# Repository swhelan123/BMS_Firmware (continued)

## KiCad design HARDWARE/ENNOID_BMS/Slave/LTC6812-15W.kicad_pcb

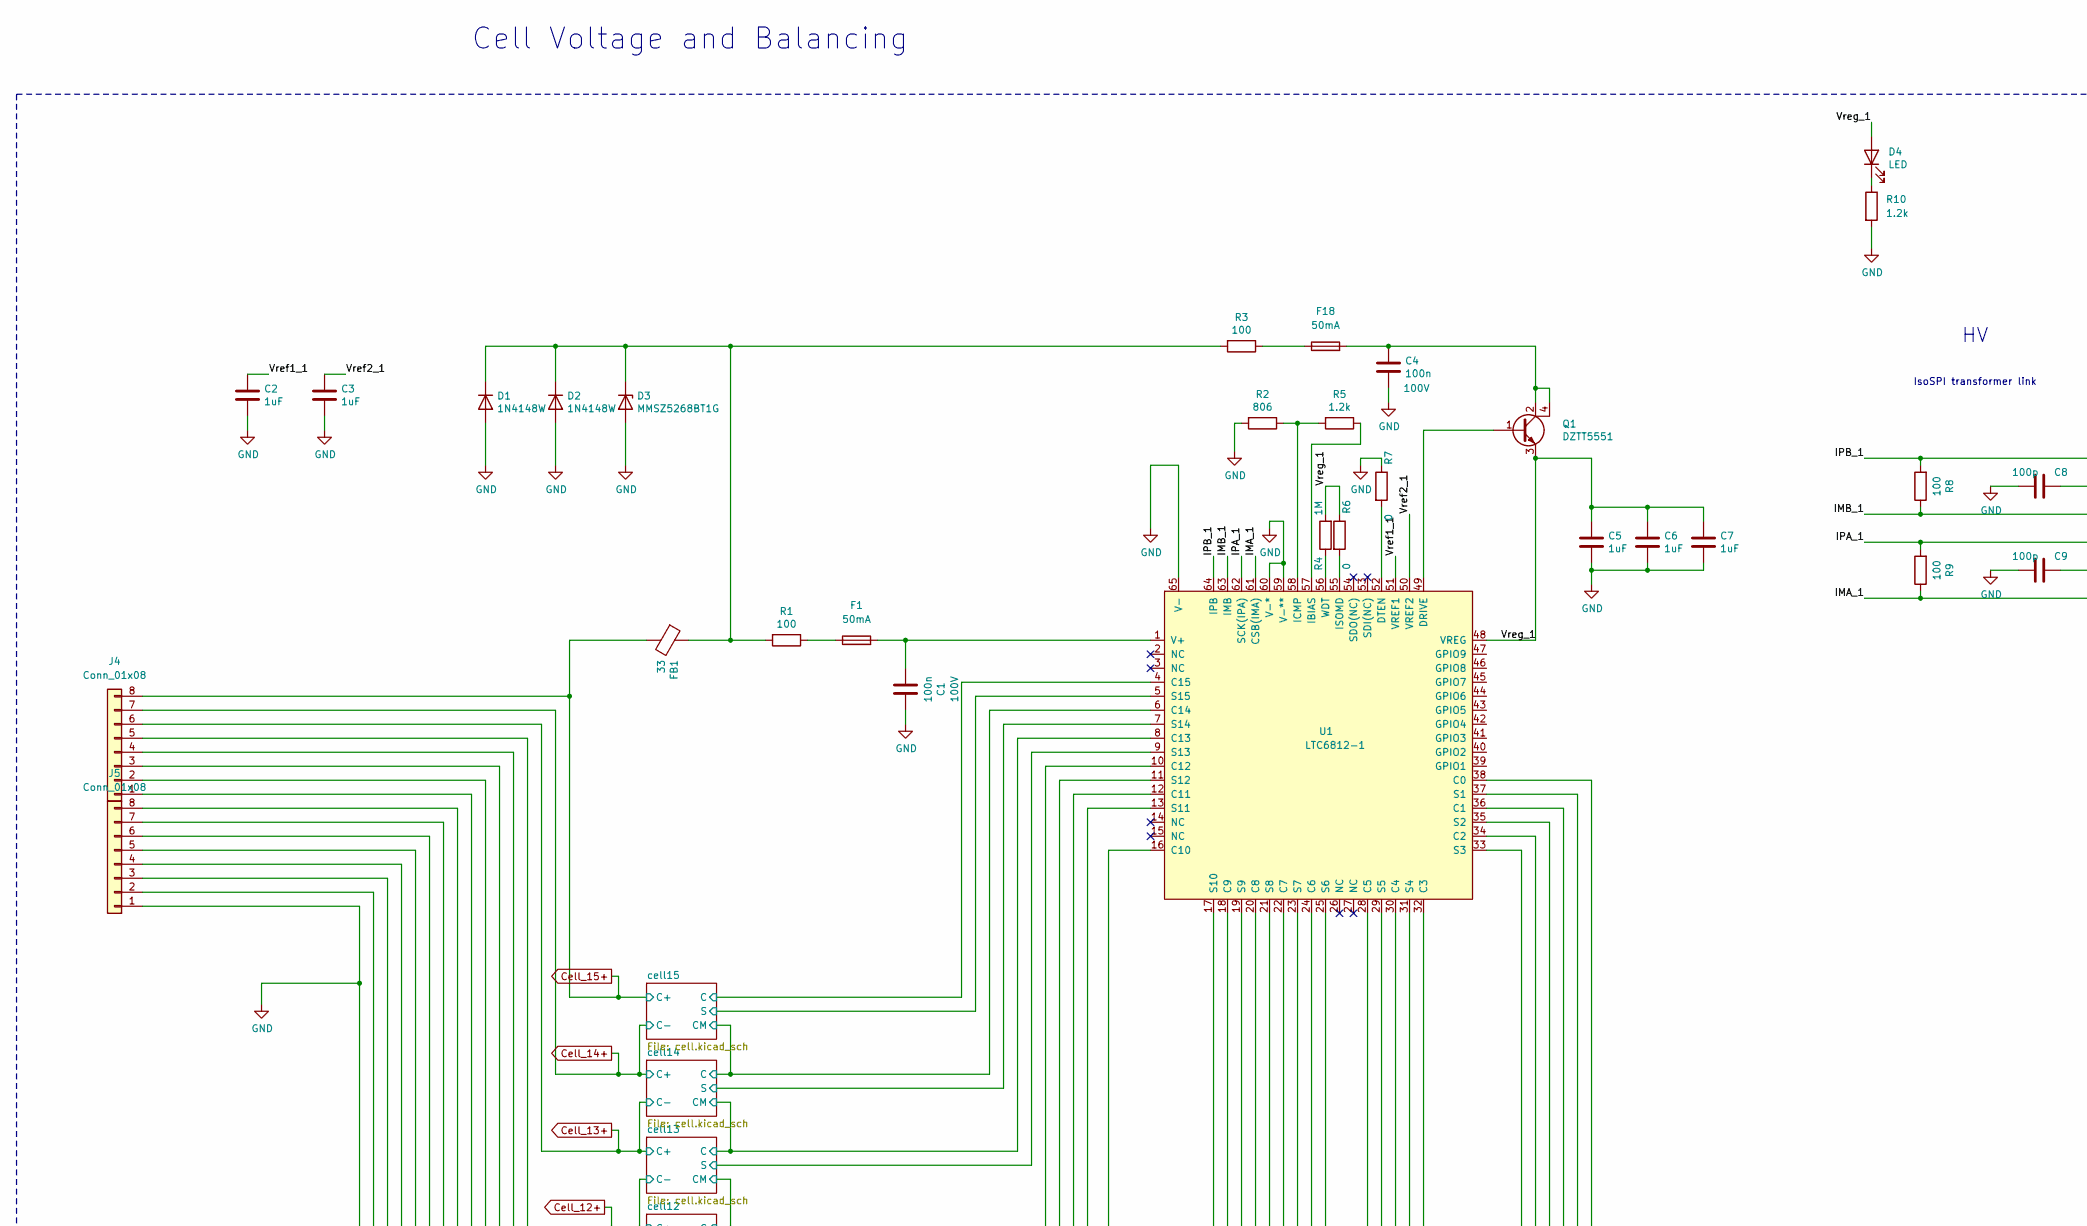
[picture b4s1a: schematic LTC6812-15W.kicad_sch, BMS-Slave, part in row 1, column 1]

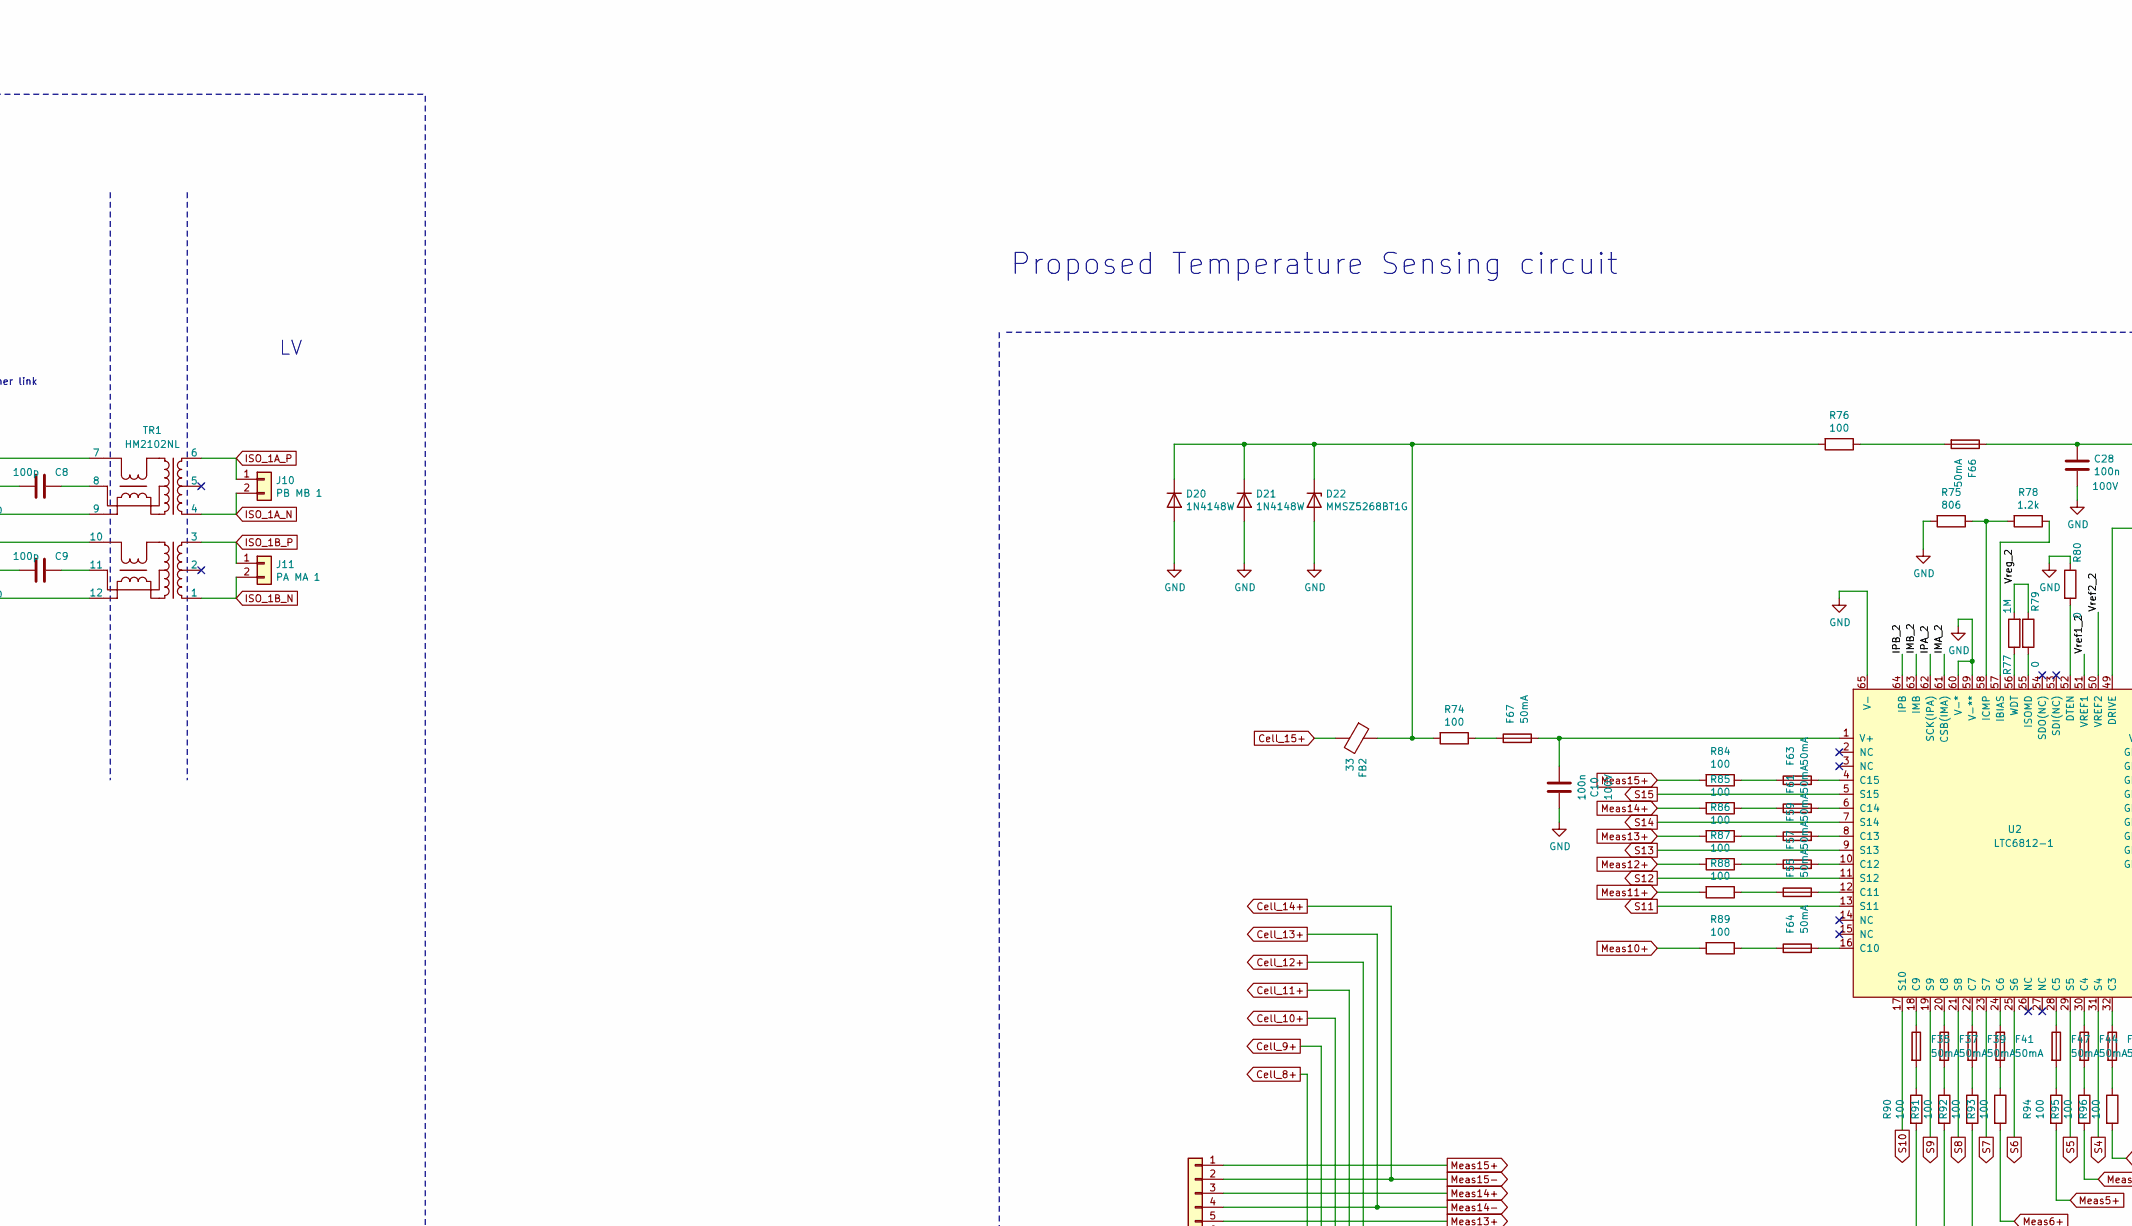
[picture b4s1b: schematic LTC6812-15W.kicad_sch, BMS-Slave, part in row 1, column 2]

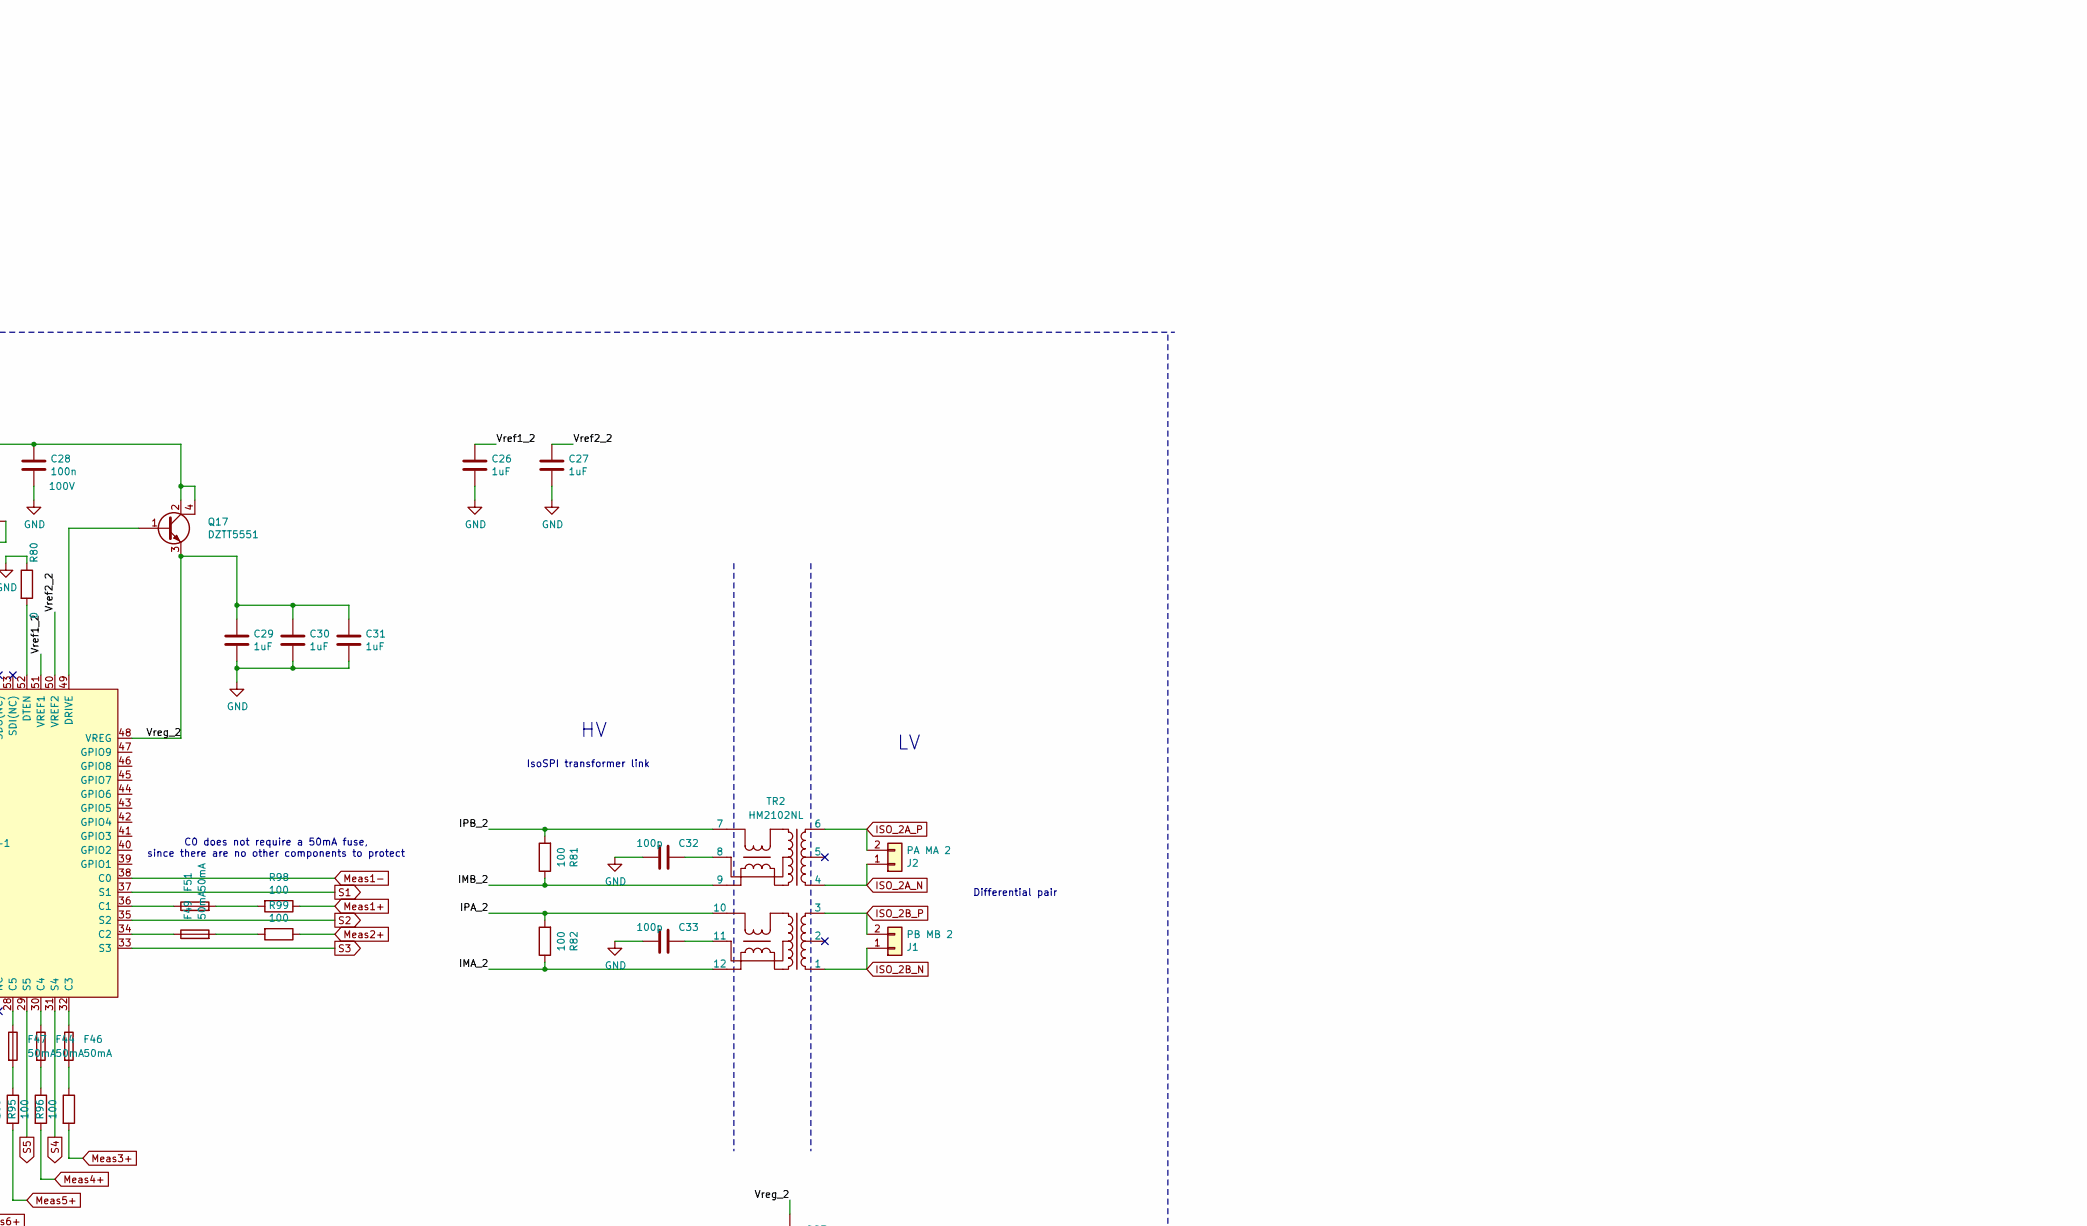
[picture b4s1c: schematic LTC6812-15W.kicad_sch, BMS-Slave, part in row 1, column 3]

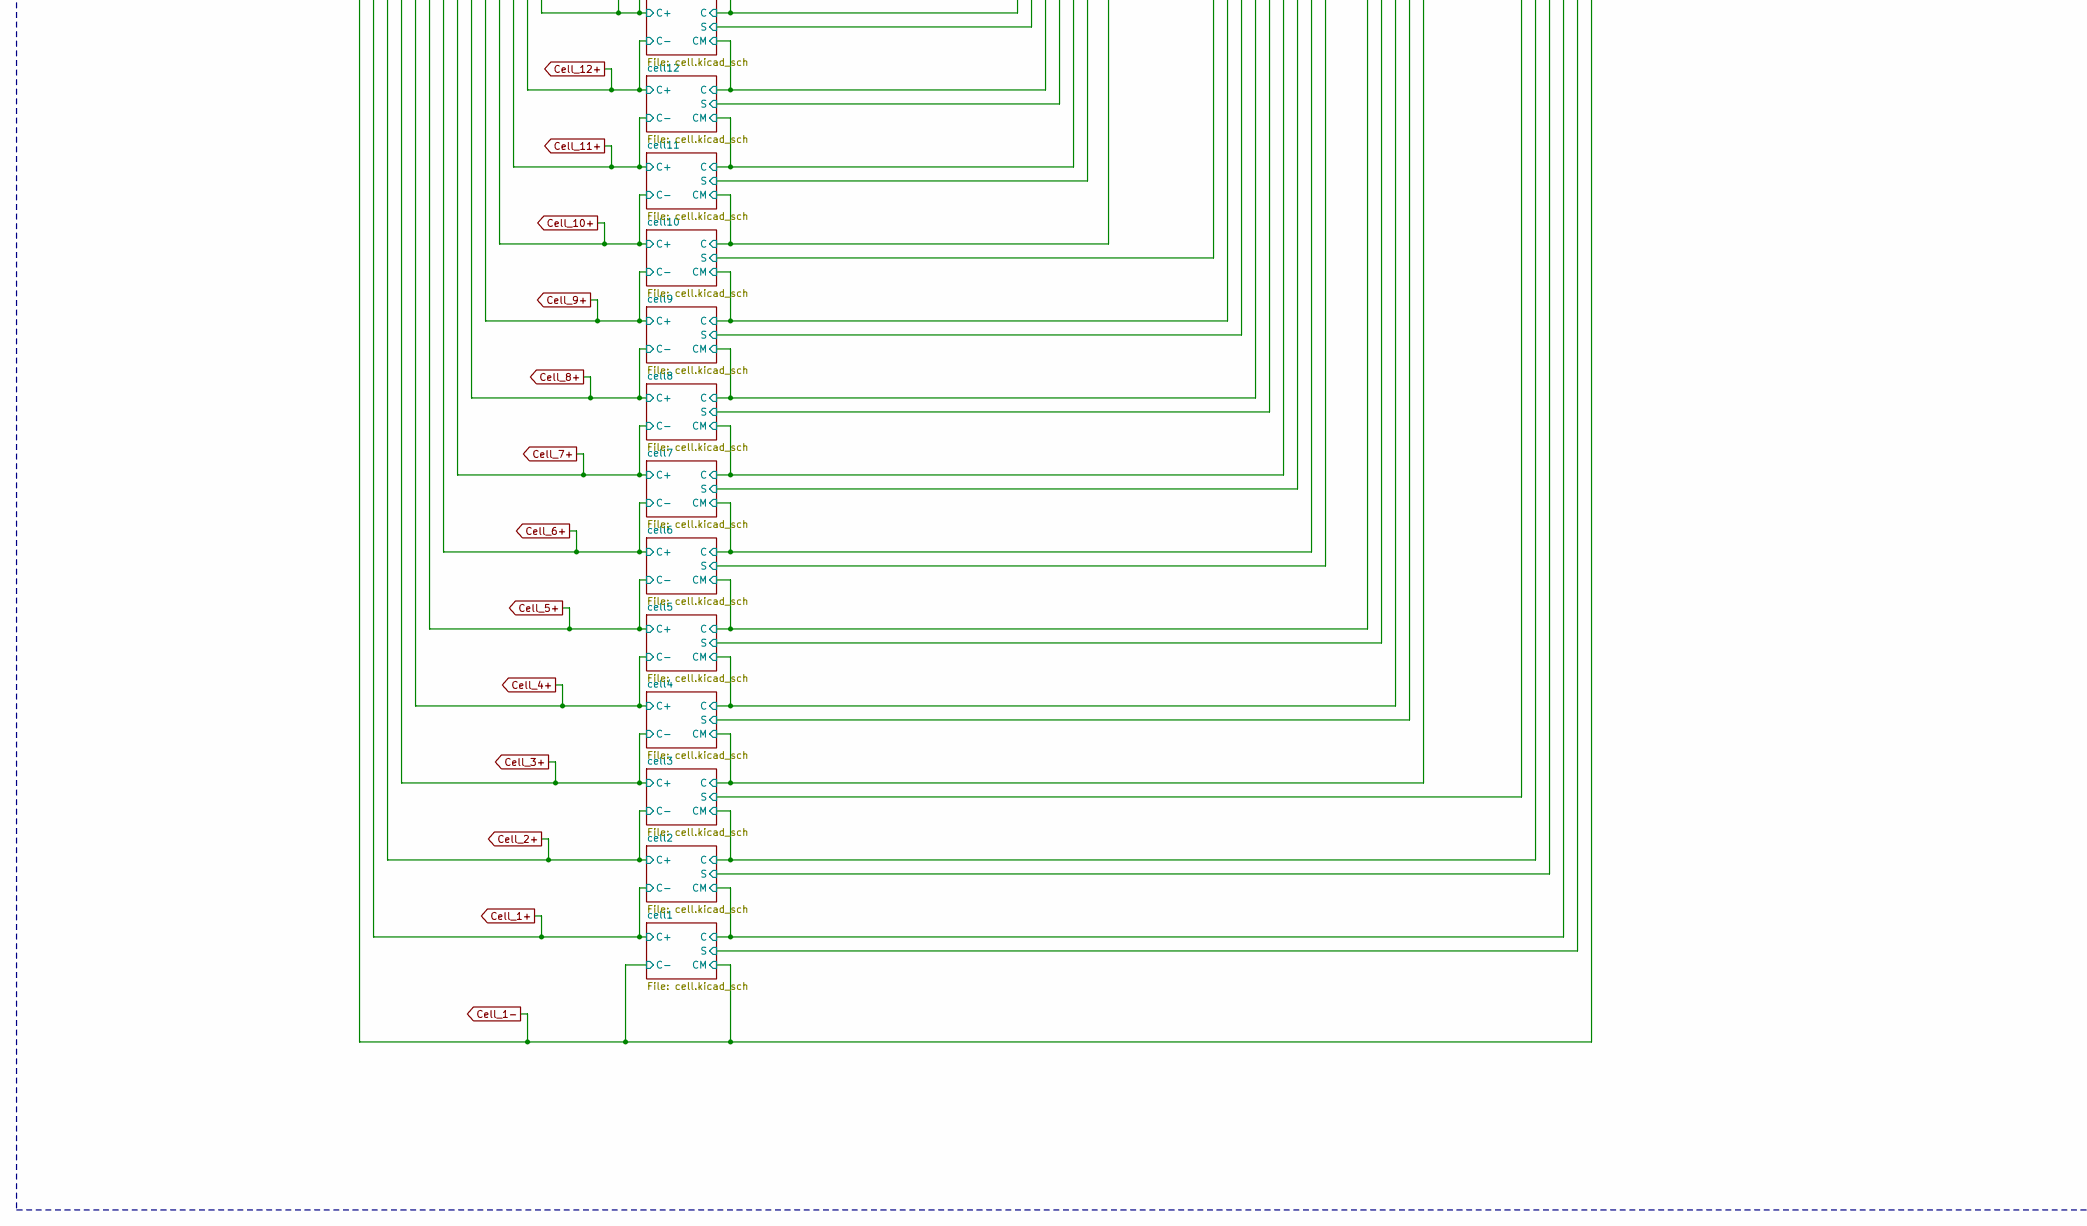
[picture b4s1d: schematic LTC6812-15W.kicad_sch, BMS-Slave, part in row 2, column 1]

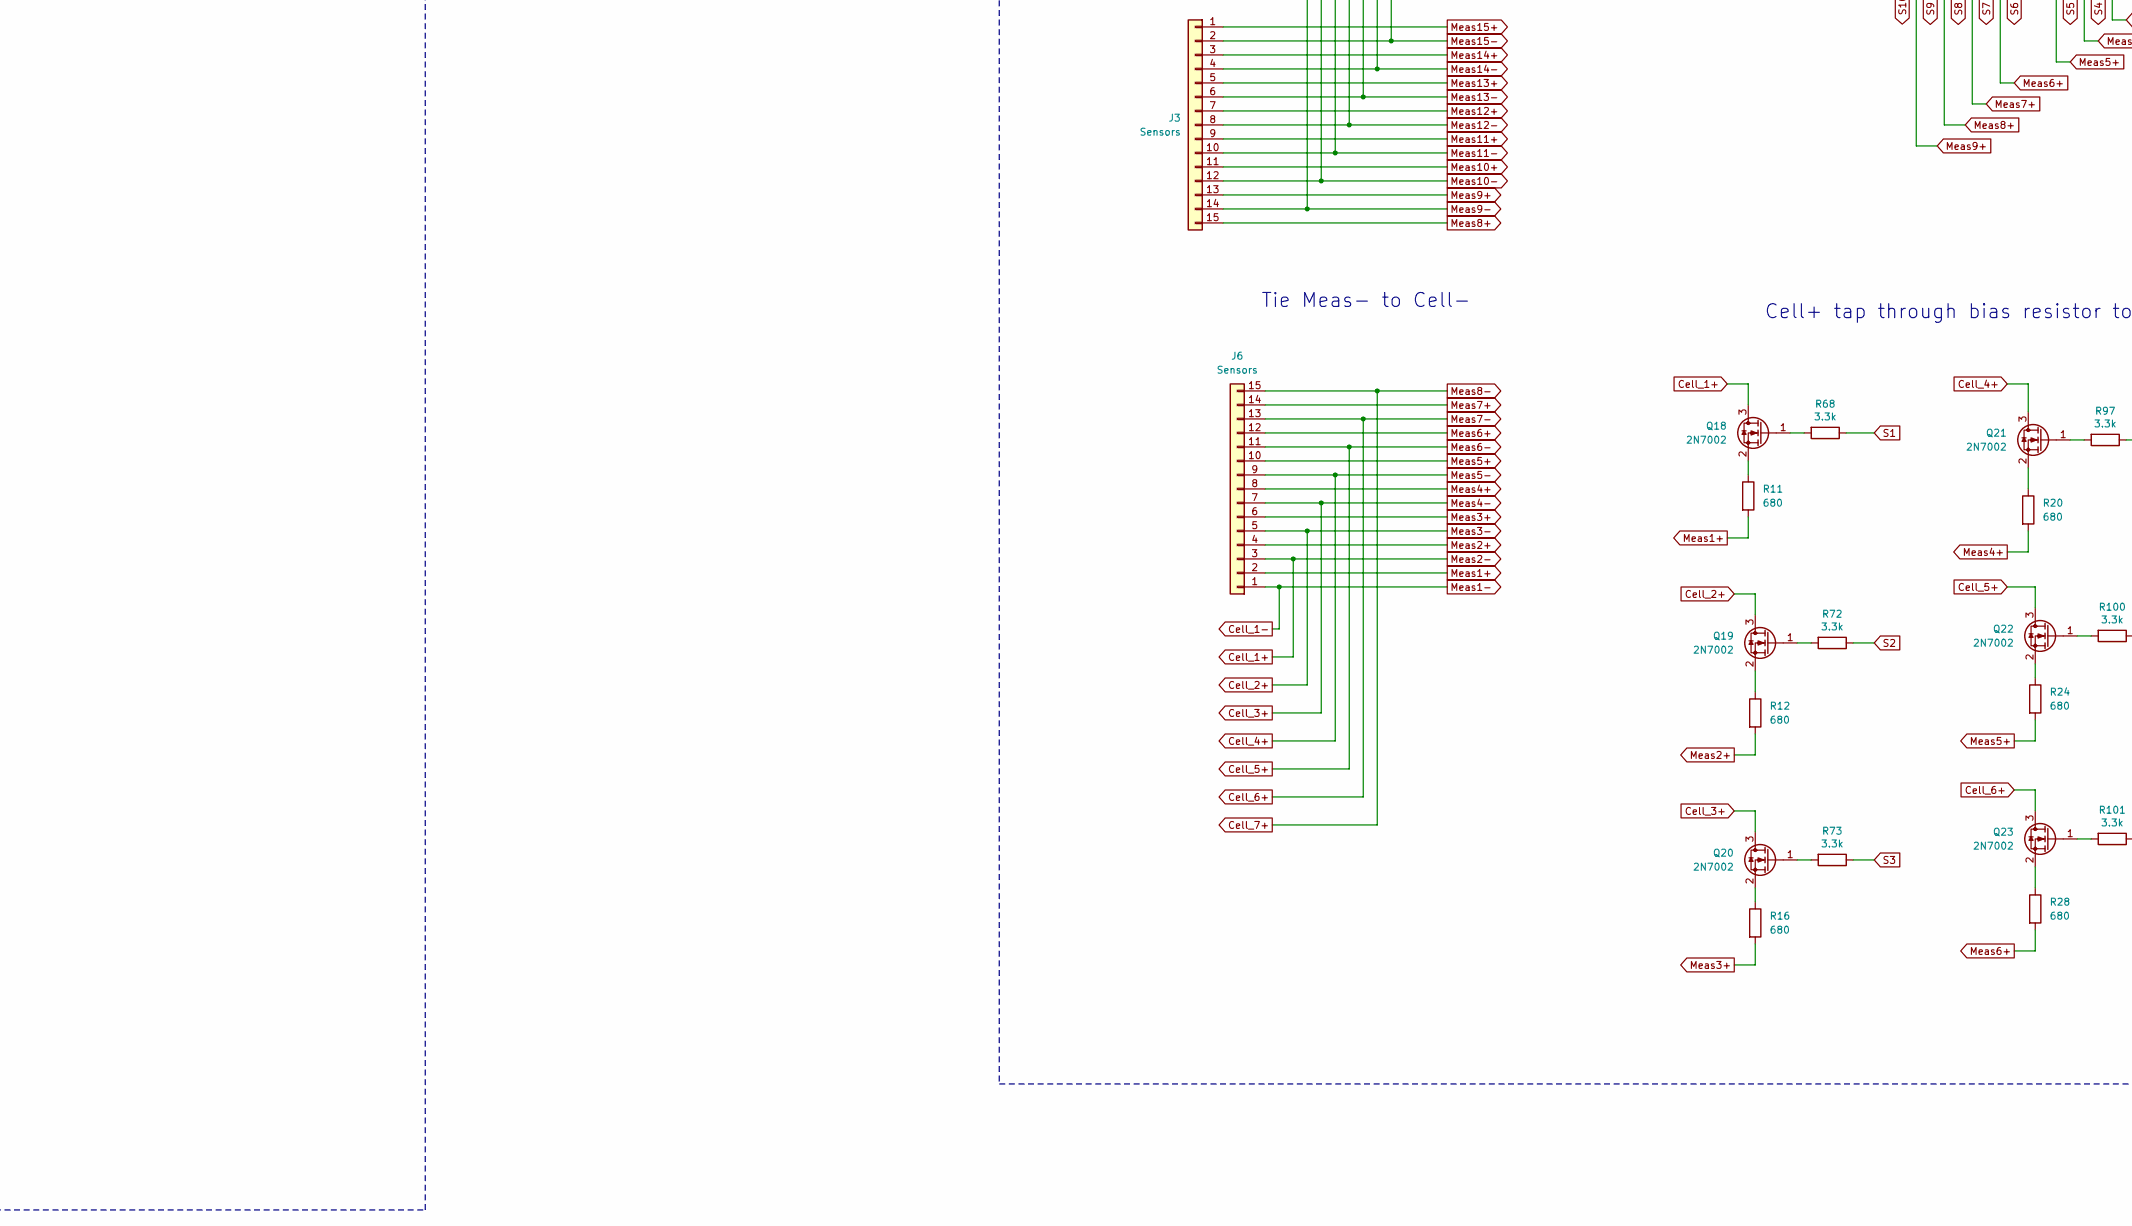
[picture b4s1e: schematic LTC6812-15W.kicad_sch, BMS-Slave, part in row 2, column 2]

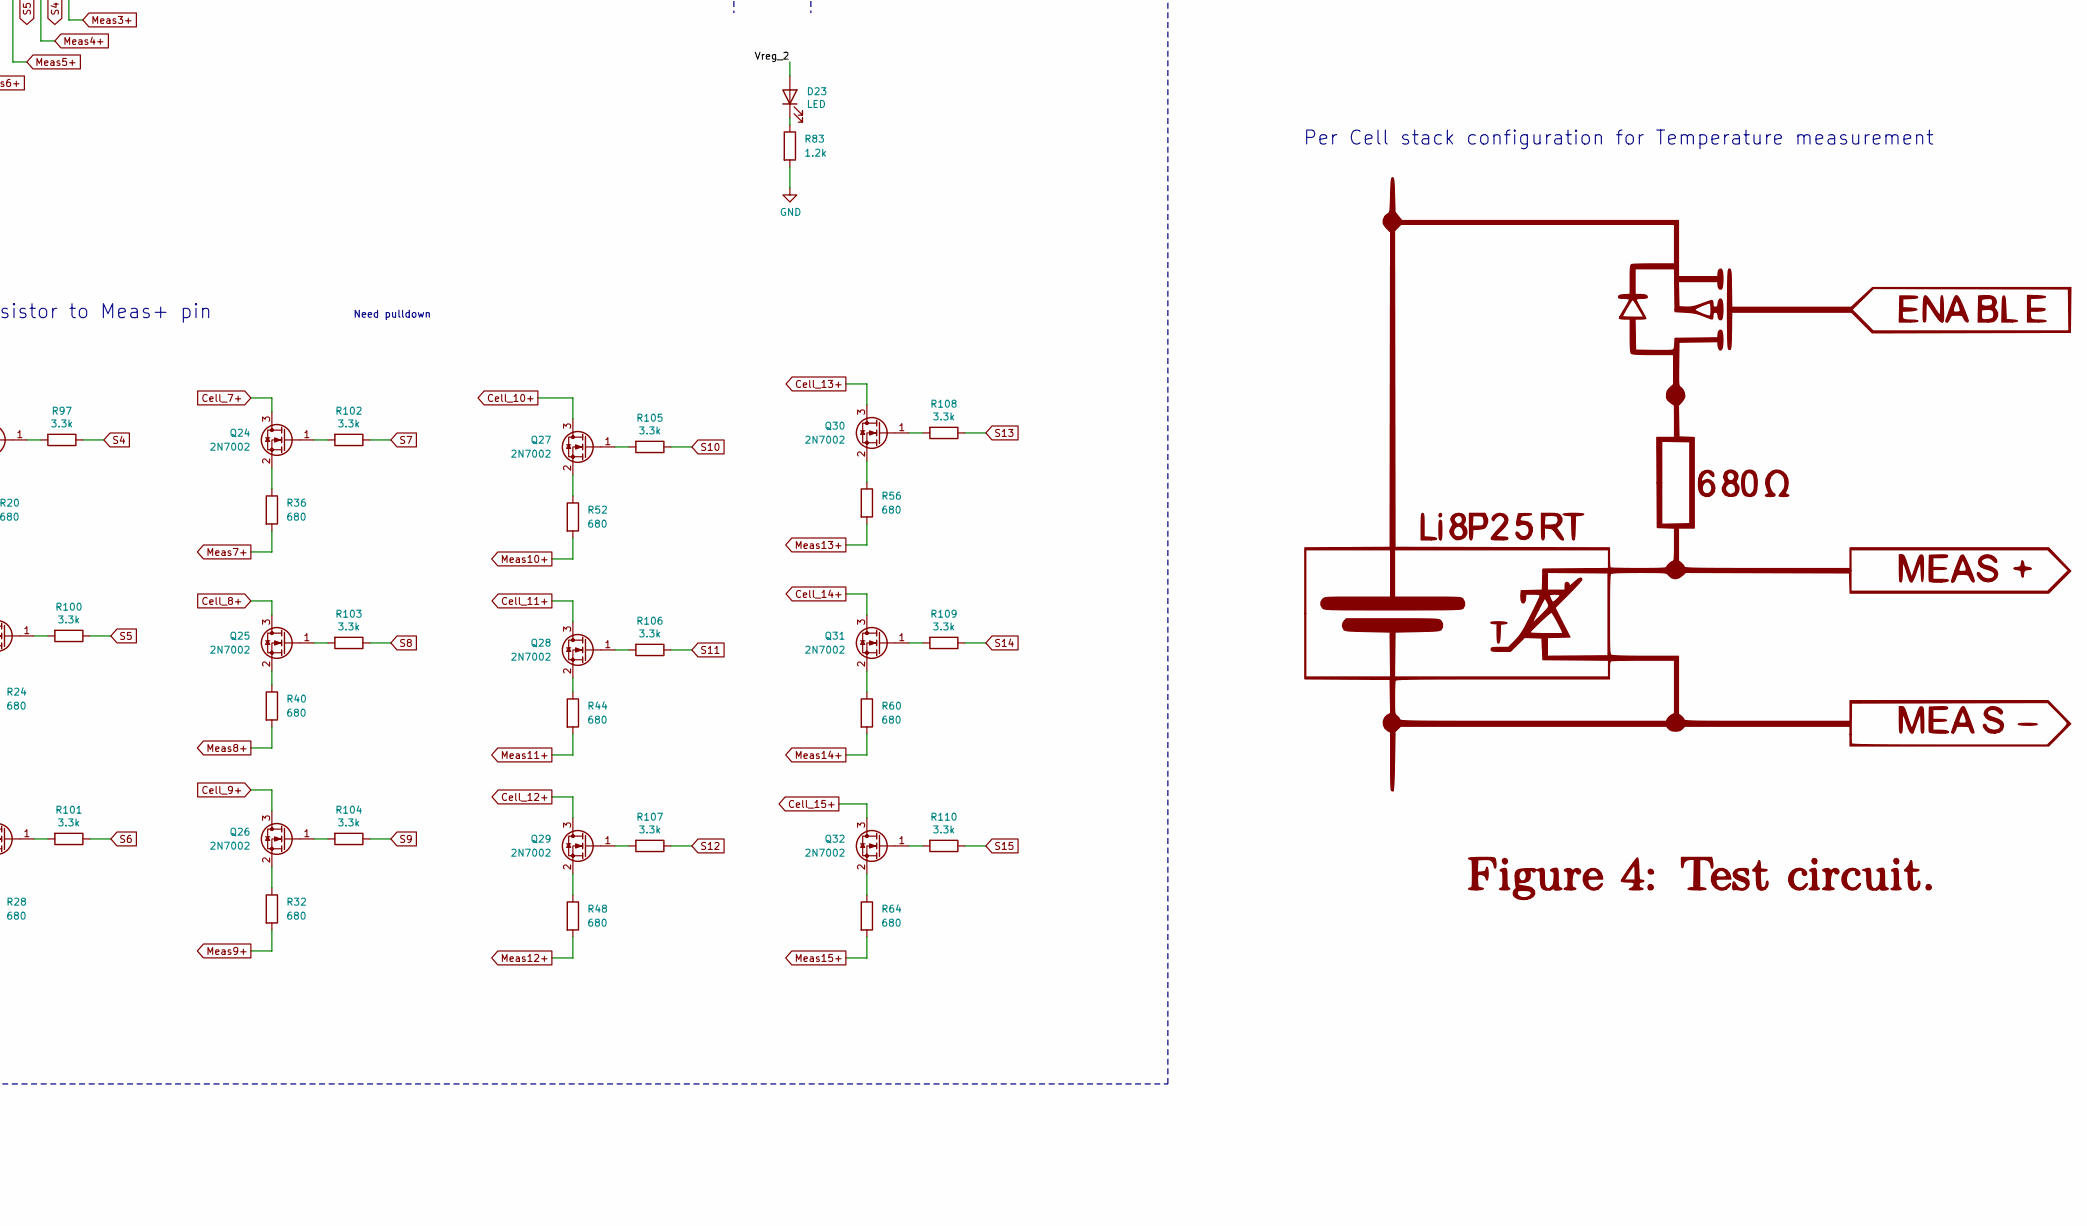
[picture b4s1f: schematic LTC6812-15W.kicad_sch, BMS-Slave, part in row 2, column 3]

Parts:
C1, C4, C10, C28: 100n; C_0603_1608Metric; Voltage 100V; Part Number GRM188R72A104KA35D
C2, C3, C5, C6, C7, C26, C27, C29, C30, C31: 1uF; C_0603_1608Metric; Part Number CL10B105KP8NNNC
C8, C9, C32, C33: 100p; C_0603_1608Metric; Part Number GRM1885C1H101JA01D
D1, D2, D20, D21: 1N4148W; D_SOD-123; Part Number 1N4148W-7-F
D3, D22: MMSZ5268BT1G; D_SOD-123; Part Number MMSZ5268BT1G
D4, D23: LED; LED_0603_1608Metric_Pad1.05x0.95mm_HandSolder; Part Number VLMTG1400-GS08
F1, F18, F35, F37, F39, F41, F44, F46, F47, F49, F51, F55, F57, F59, F61, F63, F64, F66, F67: 50mA; Fuse_1206_3216Metric; Part Number 3413.0002.11
FB1, FB2: 33; R_0603_1608Metric; Part Number BLM18PG330SN1D
J1: PB MB 2; Molex_PicoBlade_53048-0210_1x02_P1.25mm_Horizontal; Part Number 53048-0210
J2: PA MA 2; Molex_PicoBlade_53048-0210_1x02_P1.25mm_Horizontal; Part Number 53048-0210
J3, J6: Sensors; Molex_PicoBlade_53048-1510_1x15_P1.25mm_Horizontal; Part Number 53048-1510
J4, J5: Conn_01x08; Molex_PicoBlade_53048-0810_1x08_P1.25mm_Horizontal; Part Number 53048-0810
J10: PB MB 1; Molex_PicoBlade_53048-0210_1x02_P1.25mm_Horizontal; Part Number 53048-0210
J11: PA MA 1; Molex_PicoBlade_53048-0210_1x02_P1.25mm_Horizontal; Part Number 53048-0210
Q1, Q17: DZTT5551; SOT-223; Part Number DZT5551-13
Q18, Q19, Q20, Q21, Q22, Q23, Q24, Q25, Q26, Q27, Q28, Q29, Q30, Q31, Q32: 2N7002; SOT-23; Part Number 2N7002
R1, R3, R8, R9, R74, R76, R81, R82, R84, R85, R86, R87, R88, R89, R90, R91, R92, R93, R94, R95, R96, R98, R99: 100; R_0805_2012Metric; Part Number CRCW0805100RFKEAHP
R2, R75: 806; R_0603_1608Metric; Part Number CRCW0603806RFKEA
R4, R77: 1M; R_0603_1608Metric; Part Number CRCW06031M00FKEA
R5, R10, R78, R83: 1.2k; R_0603_1608Metric; Part Number CRCW06031K20FKEA
R6, R7, R79, R80: 0; R_0603_1608Metric; Part Number CRCW06030000Z0EA
R11, R12, R16, R20, R24, R28, R32, R36, R40, R44, R48, R52, R56, R60, R64: 680; R_0603_1608Metric; Part Number RCS0603680RFKEA
R68, R72, R73, R97, R100, R101, R102, R103, R104, R105, R106, R107, R108, R109, R110: 3.3k; R_0508_1220Metric; Part Number WK73R2ATTD3301F
TR1, TR2: HM2102NL; Part Number HM2102NL
U1, U2: LTC6812-1; TQFP-64-1EP_10x10mm_P0.5mm_EP8x8mm; Part Number LTC6812-1

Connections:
/IMA_1: R9.1, TR1.12, U1.61 (CSB(IMA))
/IMA_2: R82.1, TR2.12, U2.61 (CSB(IMA))
/IMB_1: R8.1, TR1.9, U1.63 (IMB)
/IMB_2: R81.1, TR2.9, U2.63 (IMB)
/IPA_1: R9.2, TR1.10, U1.62 (SCK(IPA))
/IPA_2: R82.2, TR2.10, U2.62 (SCK(IPA))
/IPB_1: R8.2, TR1.7, U1.64 (IPB)
/IPB_2: R81.2, TR2.7, U2.64 (IPB)
/Vref1_1: C2.2, U1.51 (VREF1)
/Vref1_2: C26.2, U2.51 (VREF1)
/Vref2_1: C3.2, U1.50 (VREF2)
/Vref2_2: C27.2, U2.50 (VREF2)
/Vreg_1: C5.2, C6.2, C7.2, D4.2 (A), Q1.3 (E), R4.2, R6.1, U1.48 (VREG)
/Vreg_2: C29.2, C30.2, C31.2, D23.2 (A), Q17.3 (E), R77.2, R79.1, U2.48 (VREG)
/cell1/C: U1.36 (C1); also elsewhere on the board
/cell1/S: U1.37 (S1); also elsewhere on the board
/cell2/C: U1.34 (C2); also elsewhere on the board
/cell2/S: U1.35 (S2); also elsewhere on the board
/cell3/C: U1.32 (C3); also elsewhere on the board
/cell3/S: U1.33 (S3); also elsewhere on the board
/cell4/C: U1.30 (C4); also elsewhere on the board
/cell4/S: U1.31 (S4); also elsewhere on the board
/cell5/C: U1.28 (C5); also elsewhere on the board
/cell5/S: U1.29 (S5); also elsewhere on the board
/cell6/C: U1.24 (C6); also elsewhere on the board
/cell6/S: U1.25 (S6); also elsewhere on the board
/cell7/C: U1.22 (C7); also elsewhere on the board
/cell7/S: U1.23 (S7); also elsewhere on the board
/cell8/C: U1.20 (C8); also elsewhere on the board
/cell8/S: U1.21 (S8); also elsewhere on the board
/cell9/S: U1.19 (S9); also elsewhere on the board
/cell10/C: U1.16 (C10); also elsewhere on the board
/cell10/CM: U1.18 (C9); also elsewhere on the board
/cell10/S: U1.17 (S10); also elsewhere on the board
/cell11/C: U1.12 (C11); also elsewhere on the board
/cell11/S: U1.13 (S11); also elsewhere on the board
/cell12/C: U1.10 (C12); also elsewhere on the board
/cell12/S: U1.11 (S12); also elsewhere on the board
/cell13/C: U1.8 (C13); also elsewhere on the board
/cell13/S: U1.9 (S13); also elsewhere on the board
/cell14/C: U1.6 (C14); also elsewhere on the board
/cell14/S: U1.7 (S14); also elsewhere on the board
/cell15/C: U1.4 (C15); also elsewhere on the board
/cell15/S: U1.5 (S15); also elsewhere on the board
Cell_1+: J5.2, J6.3, Q18.3 (D); also elsewhere on the board
Cell_1-: C1.1, C2.1, C3.1, C4.1, C5.1, C6.1, C7.1, C8.1, C9.1, C10.1, C26.1, C27.1, C28.1, C29.1, C30.1, C31.1, C32.1, C33.1, D1.2 (A), D2.2 (A), D3.2 (A), D20.2 (A), D21.2 (A), D22.2 (A), J5.1, J6.1, R2.2, R7.1, R10.2, R75.2, R80.1, R83.2, U1.38 (C0), U1.59 (V-**), U1.60 (V-*), U1.65 (V-), U2.38 (C0), U2.59 (V-**), U2.60 (V-*), U2.65 (V-); also elsewhere on the board
Cell_2+: J5.3, J6.5, Q19.3 (D); also elsewhere on the board
Cell_3+: J5.4, J6.7, Q20.3 (D); also elsewhere on the board
Cell_4+: J5.5, J6.9, Q21.3 (D); also elsewhere on the board
Cell_5+: J5.6, J6.11, Q22.3 (D); also elsewhere on the board
Cell_6+: J5.7, J6.13, Q23.3 (D); also elsewhere on the board
Cell_7+: J5.8, J6.15, Q24.3 (D); also elsewhere on the board
Cell_8+: J3.14, J4.1, Q25.3 (D); also elsewhere on the board
Cell_9+: J3.12, J4.2, Q26.3 (D); also elsewhere on the board
Cell_10+: J3.10, J4.3, Q27.3 (D); also elsewhere on the board
Cell_11+: J3.8, J4.4, Q28.3 (D); also elsewhere on the board
Cell_12+: J3.6, J4.5, Q29.3 (D); also elsewhere on the board
Cell_13+: J3.4, J4.6, Q30.3 (D); also elsewhere on the board
Cell_14+: J3.2, J4.7, Q31.3 (D); also elsewhere on the board
Cell_15+: FB1.2, FB2.2, J4.8, Q32.3 (D); also elsewhere on the board
ISO_1A_N: J10.2, TR1.4
ISO_1A_P: J10.1, TR1.6
ISO_1B_N: J11.2, TR1.1
ISO_1B_P: J11.1, TR1.3
ISO_2A_N: J2.1, TR2.4
ISO_2A_P: J2.2, TR2.6
ISO_2B_N: J1.1, TR2.1
ISO_2B_P: J1.2, TR2.3
Meas1+: J6.2, R11.2, R98.1
Meas2+: J6.4, R12.2, R99.1
Meas3+: J6.6, R16.2, R96.2
Meas4+: J6.8, R20.2, R95.2
Meas5+: J6.10, R24.2, R94.2
Meas6+: J6.12, R28.2, R93.2
Meas7+: J6.14, R36.2, R92.2
Meas8+: J3.15, R40.2, R91.2
Meas9+: J3.13, R32.2, R90.2
Meas10+: J3.11, R52.2, R89.2
Meas11+: J3.9, R44.2, R88.2
Meas12+: J3.7, R48.2, R87.2
Meas13+: J3.5, R56.2, R86.2
Meas14+: J3.3, R60.2, R85.2
Meas15+: J3.1, R64.2, R84.2
unnamed: C4.2, F18.2, Q1.2 (C), Q1.4 (C)
unnamed: C8.2, TR1.8
unnamed: C9.2, TR1.11
unnamed: C28.2, F66.1, Q17.2 (C), Q17.4 (C)
unnamed: C32.2, TR2.8
unnamed: C33.2, TR2.11
unnamed: D1.1 (K), D2.1 (K), D3.1 (K), FB1.1, R1.2, R3.2
unnamed: D4.1 (K), R10.1
unnamed: D20.1 (K), D21.1 (K), D22.1 (K), FB2.1, R74.2, R76.2
unnamed: D23.1 (K), R83.1
unnamed: F1.1, R1.1
unnamed: F18.1, R3.1
unnamed: F35.2, R90.1
unnamed: F37.2, R91.1
unnamed: F39.2, R92.1
unnamed: F41.2, R93.1
unnamed: F44.2, R95.1
unnamed: F46.2, R96.1
unnamed: F47.2, R94.1
unnamed: F49.2, R99.2
unnamed: F51.2, R98.2
unnamed: F55.1, R88.1
unnamed: F57.1, R87.1
unnamed: F59.1, R86.1
unnamed: F61.1, R85.1
unnamed: F63.1, R84.1
unnamed: F64.1, R89.1
unnamed: F66.2, R76.1
unnamed: F67.1, R74.1
unnamed: Q1.1 (B), U1.49 (DRIVE)
unnamed: Q17.1 (B), U2.49 (DRIVE)
unnamed: Q18.1 (G), R68.2
unnamed: Q18.2 (S), R11.1
unnamed: Q19.1 (G), R72.2
unnamed: Q19.2 (S), R12.1
unnamed: Q20.1 (G), R73.2
unnamed: Q20.2 (S), R16.1
unnamed: Q21.1 (G), R97.2
unnamed: Q21.2 (S), R20.1
unnamed: Q22.1 (G), R100.2
unnamed: Q22.2 (S), R24.1
unnamed: Q23.1 (G), R101.2
unnamed: Q23.2 (S), R28.1
unnamed: Q24.1 (G), R102.2
unnamed: Q24.2 (S), R36.1
unnamed: Q25.1 (G), R103.2
unnamed: Q25.2 (S), R40.1
unnamed: Q26.1 (G), R104.2
unnamed: Q26.2 (S), R32.1
unnamed: Q27.1 (G), R105.2
unnamed: Q27.2 (S), R52.1
unnamed: Q28.1 (G), R106.2
unnamed: Q28.2 (S), R44.1
unnamed: Q29.1 (G), R107.2
unnamed: Q29.2 (S), R48.1
unnamed: Q30.1 (G), R108.2
unnamed: Q30.2 (S), R56.1
unnamed: Q31.1 (G), R109.2
unnamed: Q31.2 (S), R60.1
unnamed: Q32.1 (G), R110.2
unnamed: Q32.2 (S), R64.1
unnamed: R7.2, U1.52 (DTEN)
unnamed: R5.1, U1.57 (IBIAS)
unnamed: R2.1, R5.2, U1.58 (ICMP)
unnamed: R6.2, U1.55 (ISOMD)
unnamed: C1.2, F1.2, U1.1 (V+)
unnamed: R4.1, U1.56 (WDT)
unnamed: F51.1, U2.36 (C1)
unnamed: F49.1, U2.34 (C2)
unnamed: F46.1, U2.32 (C3)
unnamed: F44.1, U2.30 (C4)
unnamed: F47.1, U2.28 (C5)
unnamed: F41.1, U2.24 (C6)
unnamed: F39.1, U2.22 (C7)
unnamed: F37.1, U2.20 (C8)
unnamed: F35.1, U2.18 (C9)
unnamed: F64.2, U2.16 (C10)
unnamed: F55.2, U2.12 (C11)
unnamed: F57.2, U2.10 (C12)
unnamed: F59.2, U2.8 (C13)
unnamed: F61.2, U2.6 (C14)
unnamed: F63.2, U2.4 (C15)
unnamed: R80.2, U2.52 (DTEN)
unnamed: R78.1, U2.57 (IBIAS)
unnamed: R75.1, R78.2, U2.58 (ICMP)
unnamed: R79.2, U2.55 (ISOMD)
unnamed: C10.2, F67.2, U2.1 (V+)
unnamed: R77.1, U2.56 (WDT)
S1: R68.1, U2.37 (S1)
S2: R72.1, U2.35 (S2)
S3: R73.1, U2.33 (S3)
S4: R97.1, U2.31 (S4)
S5: R100.1, U2.29 (S5)
S6: R101.1, U2.25 (S6)
S7: R102.1, U2.23 (S7)
S8: R103.1, U2.21 (S8)
S9: R104.1, U2.19 (S9)
S10: R105.1, U2.17 (S10)
S11: R106.1, U2.13 (S11)
S12: R107.1, U2.11 (S12)
S13: R108.1, U2.9 (S13)
S14: R109.1, U2.7 (S14)
S15: R110.1, U2.5 (S15)

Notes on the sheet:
Differential pair
Per Cell stack configuration for Temperature measurement
Need pulldown
Cell Voltage and Balancing
Tie Meas- to Cell-
C0 does not require a 50mA fuse, since there are no other components to protect
Cell+ tap through bias resistor to Meas+ pin
Proposed Temperature Sensing circuit
IsoSPI transformer link
